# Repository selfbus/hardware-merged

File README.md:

<h1>Selfbus Hardware</h1>
<h2>Main-Branch</h2>
This branch contains <b>all</b> Selfbus hardware items which are needed to build up KNX devices: different types of PCBs, 3D printable tools and enclosures. 

<h2>Other Branches</h2>
Experimental development shall be done within a seperate branch to prevent the main branch getting spammed with dev-commits. 

<h3>Folder structure</h3>
<ul>
<li> addons - item / part / pcb which adds additional functions to a controller, application or module 
<li> applications - applications/devices that require an additional controller board
<li> controller - controller boards
<li> module - devices that do not require a controller board. The controller and the app are merged within one PCB. 
<li> misc - other stuff that is not an EIB bus device
<li> tool - helpers with no functionality without another item
</ul>

<h3>Abbreviations</h3>
<ul>
<li>FM - flush mount (UP Unterputz)
<li>DIN - din rail mountable (für Hutschieneninstallation)
<li>MU - module units (TE Teilungseinheiten); indicates how much space a DIN rail device needs 
<li>*lpc922* - module or controller with lpc922 µC
<li>*lpc1115* - module or controller with lpc1115 µC
<li>TOP / MID / BOT - position where in a DIN rail enclosure a PCB will be mounted
</ul>

<h2>Releases</h2>
The unversioned *.sch and *.brd files indicate development files. 
Once a new version is released, a corresponding folder will be created and copy of the files with the release version appended to the file name will be stored in that folder as well as all other files connected directly to that version (iBom, labels, etc.).

<b>Example: </b>https://github.com/selfbus/hardware-merged/tree/main/modules_lpc1115/smokedetector <br/>
But keep in mind, that this is not implemented in each and every project. In fact it's the exception today (11.05.2023) since a lot of projects are existing within this repository. 
  
<h2>Identify mature hardware</h2>
A warning hint within the readme.md was placed in nearly all projects taken over from hardware-incubation. A folder without that hint contains most likely a stable version taken over from the "hardware" repository. If you are not sure: search for documentation for that device or item at https://selfbus.org or ask the community via https://selfbus.org/forum or https://selfbus.org/chat.

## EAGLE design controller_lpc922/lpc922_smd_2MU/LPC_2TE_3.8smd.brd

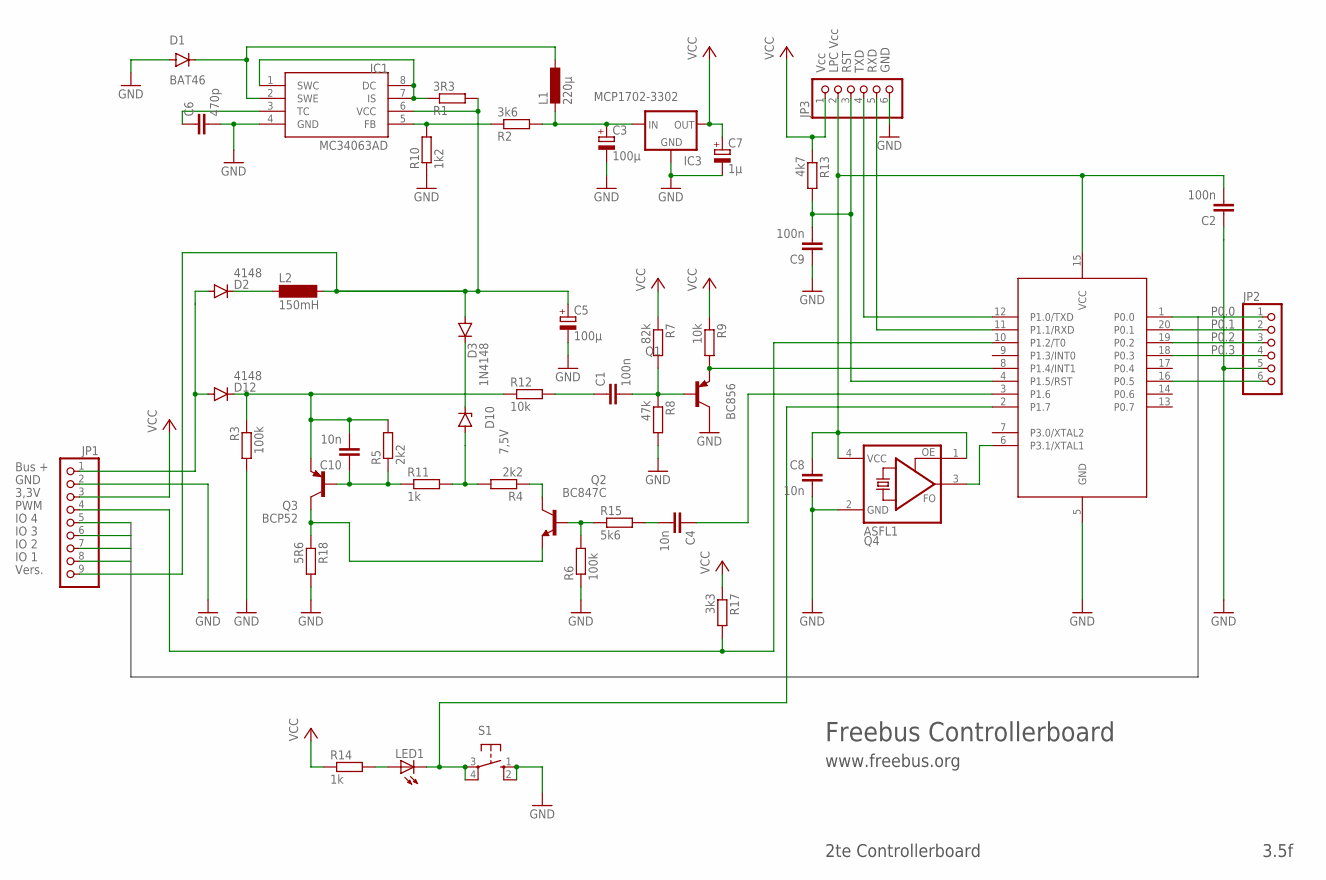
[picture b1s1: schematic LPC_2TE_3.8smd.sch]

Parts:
89LPC922: 89LPC922; DIL20
C1, C2, C9: 100n; C1206
C3: 100µ; E2,5-6
C4, C8, C10: 10n; C1206
C5: 100µ; E3,5-8
C6: 470p; C1206
C7: 1µ; E2-5
D1: BAT46; MINIMELF
D2, D12: 4148; MINIMELF
D3: 1N4148; MINIMELF
D10: 7,5V; DO35Z10
IC1: MC34063AD; SOIC8
IC3: MCP1702-3302; 79LXX
JP1: PINHD-1X9_LONG_2.54; 1X09_LONG
JP2, JP3: PINHD-1X6; 1X06
L1: 220µ; 0207/12
L2: 150mH; BS11
LED1: LED3MM
Q1: BC856; SOT23-BEC
Q2: BC847C; SOT23
Q3: BCP52; SOT223
Q4: ASFL1; ASF
R1: 3R3; R1206
R2: 3k6; R1206
R3, R6: 100k; R1206
R4, R5: 2k2; R1206
R7: 82k; R1206
R8: 47k; R1206
R9, R12: 10k; R1206
R10: 1k2; R1206
R11, R14: 1k; R1206
R13: 4k7; R1206
R15: 5k6; R1206
R17: 3k3; R1206
R18: 5R6; R1206
S1: 10-XX; B3F-10XX

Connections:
/RESET: 89LPC922.4 (P1.5/RST), C9.2, JP3.3, R13.2
BASE: C1.2, Q1.B, R7.2, R8.1
BASE_SEND: Q2.1 (B), R6.2, R15.1
EIB+: D2.A, D12.A, JP1.1
EIB_DC: C5.+, D3.A, IC1.6 (VCC), JP1.9, L2.2, R1.2
FEEDBACK: IC1.5 (FB), R2.1, R10.2
GND: 89LPC922.5 (GND), C2.1, C3.-, C5.-, C6.2, C7.-, C8.2, C9.1, D1.A, IC1.4 (GND), IC3.GND, JP1.2, JP2.5, JP3.6, Q1.C, Q4.2 (GND), R3.2, R6.1, R8.2, R10.1, R18.2, S1.1 (S), S1.2 (S1)
I_SENSE: Q2.2 (E), Q3.2 (C), Q3.4 (C), R18.1
unnamed: Q2.3 (C), R4.1
unnamed: C10.2, D12.C, Q3.3 (E), R3.1, R5.2, R12.1
unnamed: 89LPC922.6 (P3.1/XTAL1), Q4.3 (FO)
unnamed: IC1.1 (SWC), IC1.7 (IS), IC1.8 (DC), R1.1
unnamed: LED1.A, R14.2
unnamed: D2.C, L2.1
unnamed: C6.1, IC1.3 (TC)
unnamed: D3.C, D10.C
unnamed: C1.1, R12.2
unnamed: C4.2, R15.2
unnamed: C10.1, Q3.1 (B), R5.1, R11.1
P0.0: 89LPC922.1 (P0.0), JP1.8, JP2.1
P0.1: 89LPC922.20 (P0.1), JP1.7, JP2.2
P0.2: 89LPC922.19 (P0.2), JP1.6, JP2.3
P0.3: 89LPC922.18 (P0.3), JP1.5, JP2.4
P0.5: 89LPC922.16 (P0.5), JP2.6
PROG: 89LPC922.2 (P1.7), LED1.K (C), S1.3, S1.4 (P1)
PWM: 89LPC922.10 (P1.2/T0), JP1.4, R17.2
REFERENZ: D10.A, R4.2, R11.2
RXD: 89LPC922.11 (P1.1/RXD), JP3.5
SIGIN: 89LPC922.8 (P1.4/INT1), Q1.E, R9.2
SIGOUT: 89LPC922.3 (P1.6), C4.1
SWITCHED: D1.C, IC1.2 (SWE), L1.1
TXD: 89LPC922.12 (P1.0/TXD), JP3.4
VCC: C7.+, IC3.OUT, JP1.3, JP3.1, R7.1, R9.1, R13.1, R14.1, R17.1
VCC_5V: C3.+, IC3.IN, L1.2, R2.2
VCC_LPC: 89LPC922.15 (VCC), C2.2, C8.1, JP3.2, Q4.1 (OE), Q4.4 (VCC)

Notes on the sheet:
Bus +
GND
3,3V
PWM
IO 1
IO 2
IO 3
IO 4
Vcc
LPC Vcc
RST
TXD
RXD
Vers.
Freebus Controllerboard
www.freebus.org
2te Controllerboard
3.5f

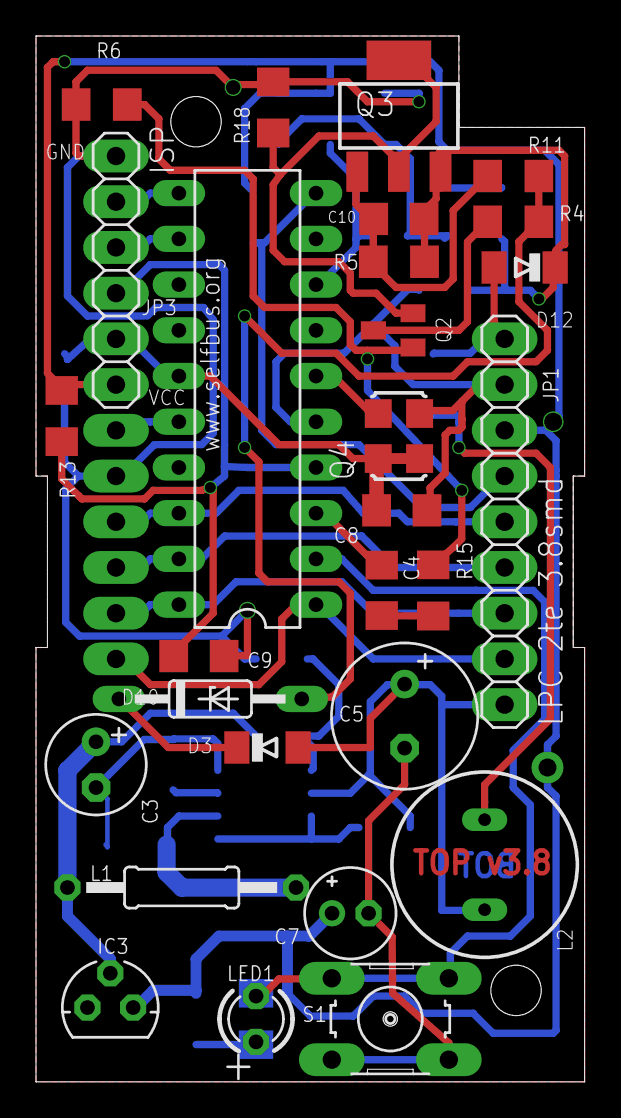
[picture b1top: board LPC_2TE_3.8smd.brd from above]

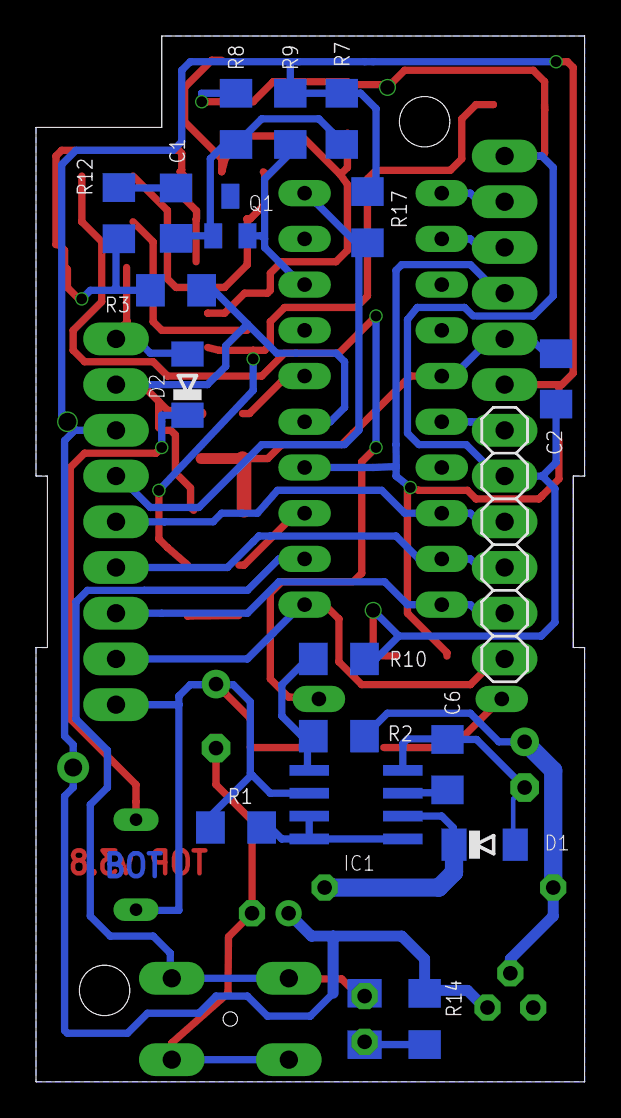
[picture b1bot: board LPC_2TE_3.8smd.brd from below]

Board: 2 copper layers, 30.5 x 58.1 mm, 46 parts (18 on the bottom side), 35 nets.

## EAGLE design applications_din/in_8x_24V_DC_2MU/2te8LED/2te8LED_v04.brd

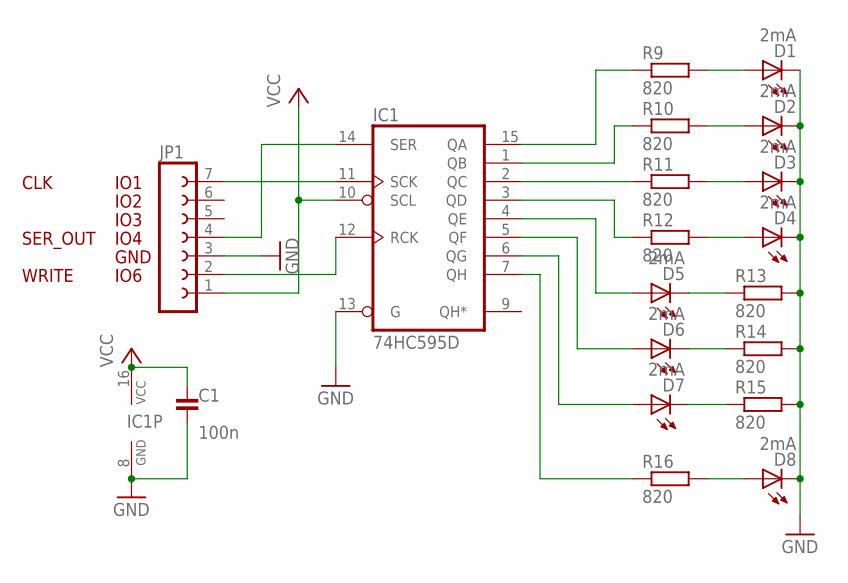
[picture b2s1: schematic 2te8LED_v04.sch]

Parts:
C1: 100n; C0805
D1, D2, D3, D4, D5, D6, D7, D8: 2mA; LED3MM
IC1: 74HC595D; SO16
JP1: FE07-1; FE07
R9, R10, R11, R12, R13, R14, R15, R16: 820; R0805

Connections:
GND: C1.2, D1.K (C), D2.K (C), D3.K (C), D4.K (C), D8.K (C), IC1.8 (GND), IC1.13 (G), JP1.3, R13.2, R14.2, R15.2
IO1: IC1.11 (SCK), JP1.7
IO4: IC1.14 (SER), JP1.4
IO6: IC1.12 (RCK), JP1.2
unnamed: IC1.15 (QA), R9.1
unnamed: IC1.1 (QB), R10.1
unnamed: IC1.2 (QC), R11.1
unnamed: IC1.3 (QD), R12.1
unnamed: D5.A, IC1.4 (QE)
unnamed: D6.A, IC1.5 (QF)
unnamed: D7.A, IC1.6 (QG)
unnamed: D1.A, R9.2
unnamed: D2.A, R10.2
unnamed: D3.A, R11.2
unnamed: D4.A, R12.2
unnamed: D5.K (C), R13.1
unnamed: D6.K (C), R14.1
unnamed: D7.K (C), R15.1
unnamed: IC1.7 (QH), R16.1
unnamed: D8.A, R16.2
VCC: C1.1, IC1.10 (SCL), IC1.16 (VCC), JP1.1

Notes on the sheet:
IO1
IO2
IO3
IO4
IO6
GND
CLK
SER_OUT
WRITE

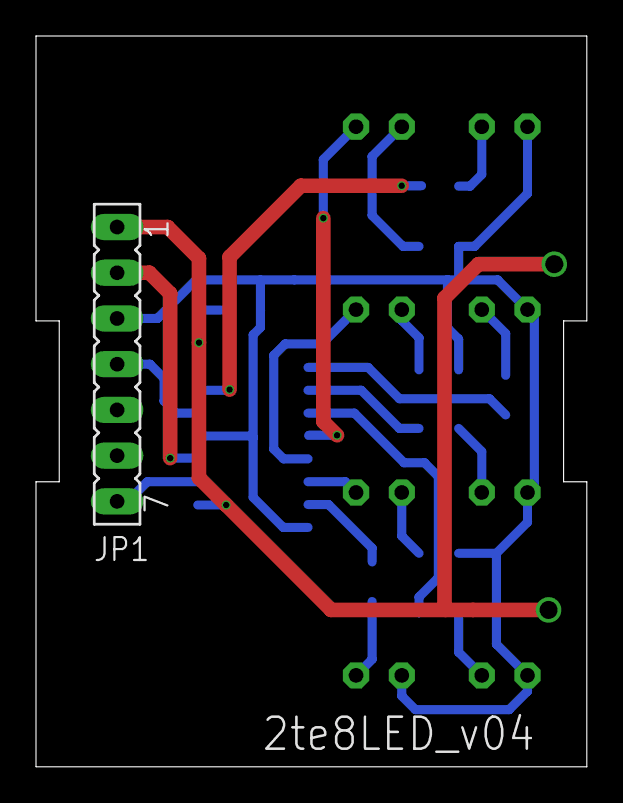
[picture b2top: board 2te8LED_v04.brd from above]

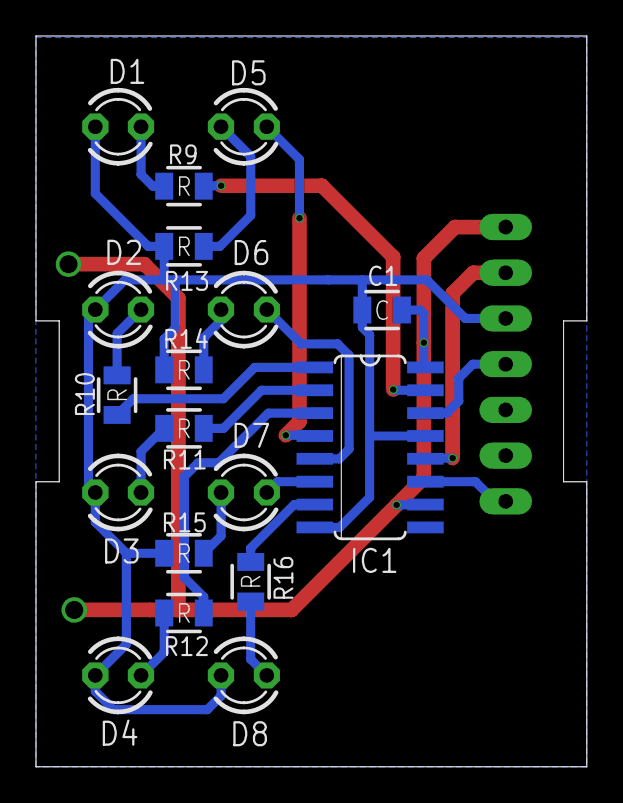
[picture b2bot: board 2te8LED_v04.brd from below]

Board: 2 copper layers, 30.6 x 40.6 mm, 19 parts (18 on the bottom side), 21 nets.

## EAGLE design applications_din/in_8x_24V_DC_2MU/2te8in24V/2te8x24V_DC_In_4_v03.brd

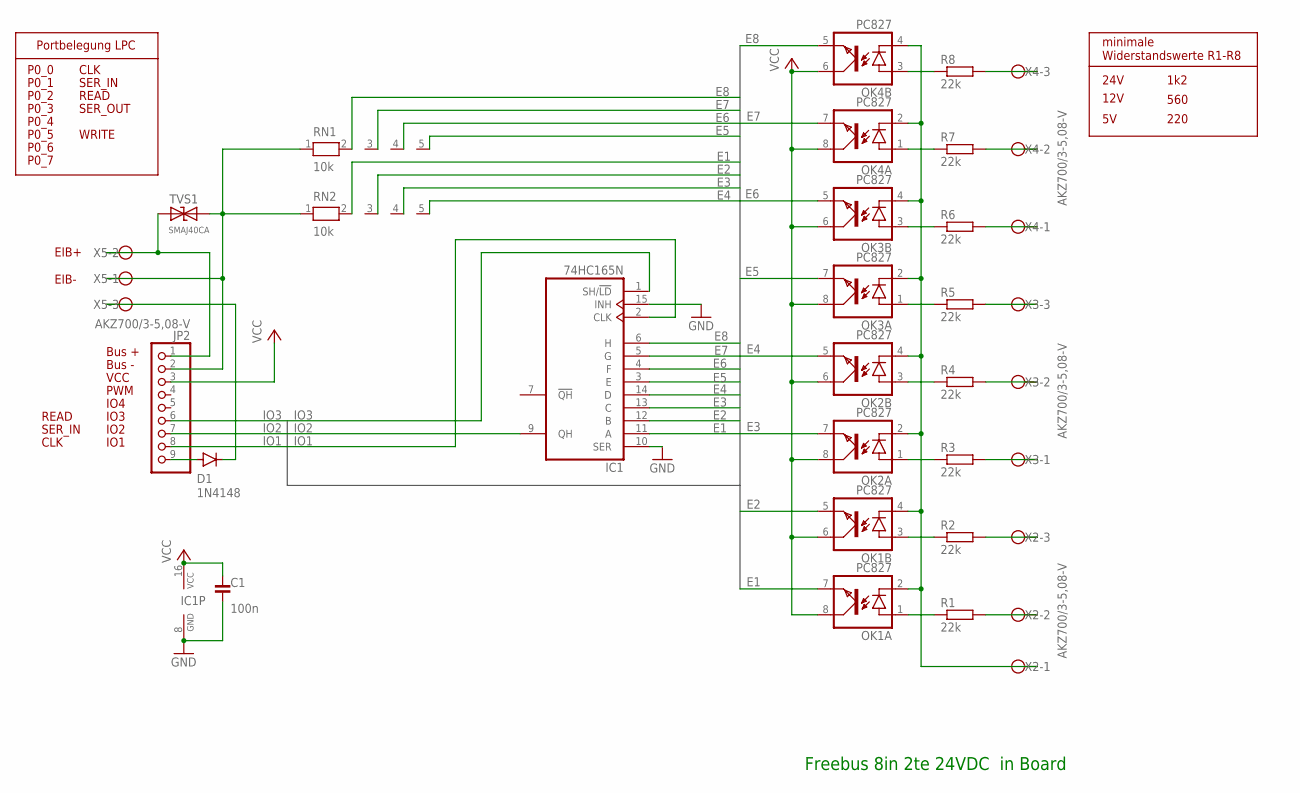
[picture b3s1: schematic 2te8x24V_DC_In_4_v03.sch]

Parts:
C1: 100n; C025-024X044
D1: 1N4148; DO35-7
IC1: 74HC165N; DIL16
JP2: PINHD-1X9; 1X09
OK1, OK2, OK3, OK4: PC827; DIL08
R1, R2, R3, R4, R5, R6, R7, R8: 22k; 0207/10
RN1, RN2: 10k; RN-5
TVS1: SMAJ40CA; DO-214AC(SMA)_BI
X2, X3, X4, X5: AKZ700/3-5,08-V

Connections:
E1: IC1.11 (A), OK1.7 (EMIT), RN2.2
E2: IC1.12 (B), OK1.5 (EMIT), RN2.3
E3: IC1.13 (C), OK2.7 (EMIT), RN2.4
E4: IC1.14 (D), OK2.5 (EMIT), RN2.5
E5: IC1.3 (E), OK3.7 (EMIT), RN1.5
E6: IC1.4 (F), OK3.5 (EMIT), RN1.4
E7: IC1.5 (G), OK4.7 (EMIT), RN1.3
E8: IC1.6 (H), OK4.5 (EMIT), RN1.2
EIB+: JP2.1, TVS1.2 (A2), X5.2
GND: C1.2, IC1.8 (GND), IC1.10 (SER), IC1.15 (INH), JP2.2, RN1.1, RN2.1, TVS1.1 (A1), X5.1
GND24: OK1.2 (C), OK1.4 (C), OK2.2 (C), OK2.4 (C), OK3.2 (C), OK3.4 (C), OK4.2 (C), OK4.4 (C), X2.1
IO1: IC1.2 (CLK), JP2.8
IO2: IC1.9 (QH), JP2.7
IO3: IC1.1 (SH/!LD), JP2.6
unnamed: D1.C, X5.3
unnamed: OK1.1 (A), R1.1
unnamed: R1.2, X2.2
unnamed: OK1.3 (A), R2.1
unnamed: R2.2, X2.3
unnamed: OK2.1 (A), R3.1
unnamed: R3.2, X3.1
unnamed: OK2.3 (A), R4.1
unnamed: R4.2, X3.2
unnamed: OK3.1 (A), R5.1
unnamed: R5.2, X3.3
unnamed: OK3.3 (A), R6.1
unnamed: R6.2, X4.1
unnamed: OK4.1 (A), R7.1
unnamed: R7.2, X4.2
unnamed: OK4.3 (A), R8.1
unnamed: R8.2, X4.3
unnamed: D1.A, JP2.9
VCC: C1.1, IC1.16 (VCC), JP2.3, OK1.6 (COL), OK1.8 (COL), OK2.6 (COL), OK2.8 (COL), OK3.6 (COL), OK3.8 (COL), OK4.6 (COL), OK4.8 (COL)

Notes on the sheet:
Freebus 8in 2te 24VDC in Board
Bus +
Bus -
VCC
PWM
IO1
IO2
IO3
IO4
SER_IN
CLK
READ
EIB+
EIB-
SER_OUT
WRITE
P0_0
P0_1
P0_2
P0_3
P0_4
P0_5
P0_6
P0_7
Portbelegung LPC
24V
12V
1k2
560
220
minimale Widerstandswerte R1-R8

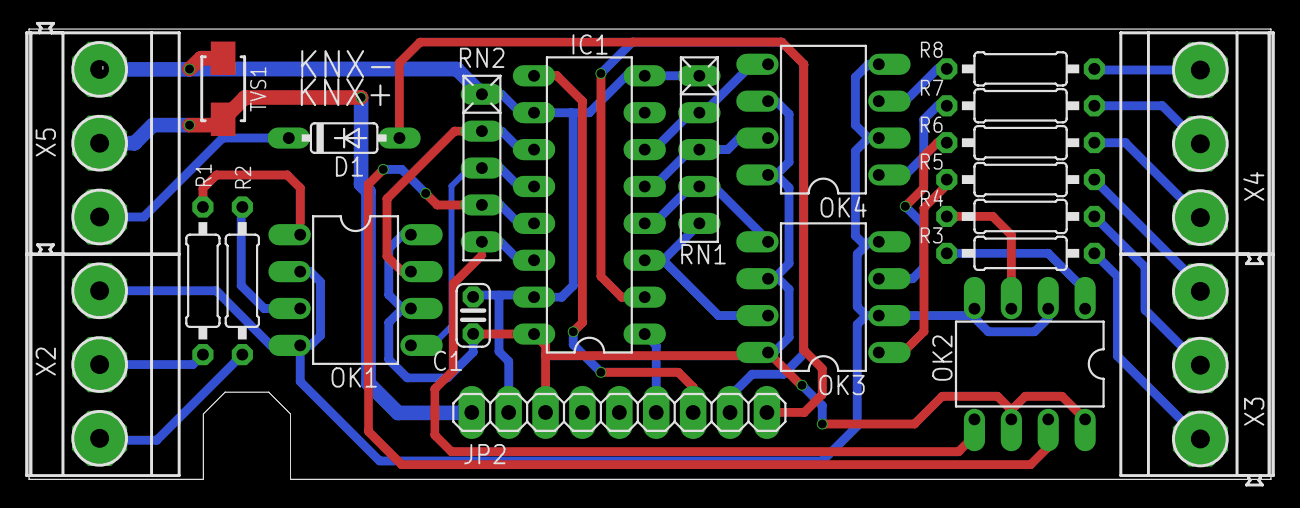
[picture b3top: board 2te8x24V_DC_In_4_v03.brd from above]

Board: 2 copper layers, 85.5 x 31.0 mm, 23 parts (0 on the bottom side), 33 nets.

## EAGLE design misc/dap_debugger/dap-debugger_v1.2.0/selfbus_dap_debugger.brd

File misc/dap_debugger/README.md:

# SBDAP - Selfbus DAP Adapter
Project documentation: https://selfbus.org/wiki/devices/tools-sonstiges/69-sbdap-selfbus-debug-adapter

Forum discussions: [https://selfbus.org/forum/app.php/tag/SBDAP](https://selfbus.org/forum/app.php/tag/SBDAP)

|Version|Description                          |
|-------|-------------------------------------|
|v1.0.0 |first release version                |
|v1.1.0 |USB-C connection instead of Micro-USB|
|v1.2.0 |IC2 package switched to SOT363/SC70  |

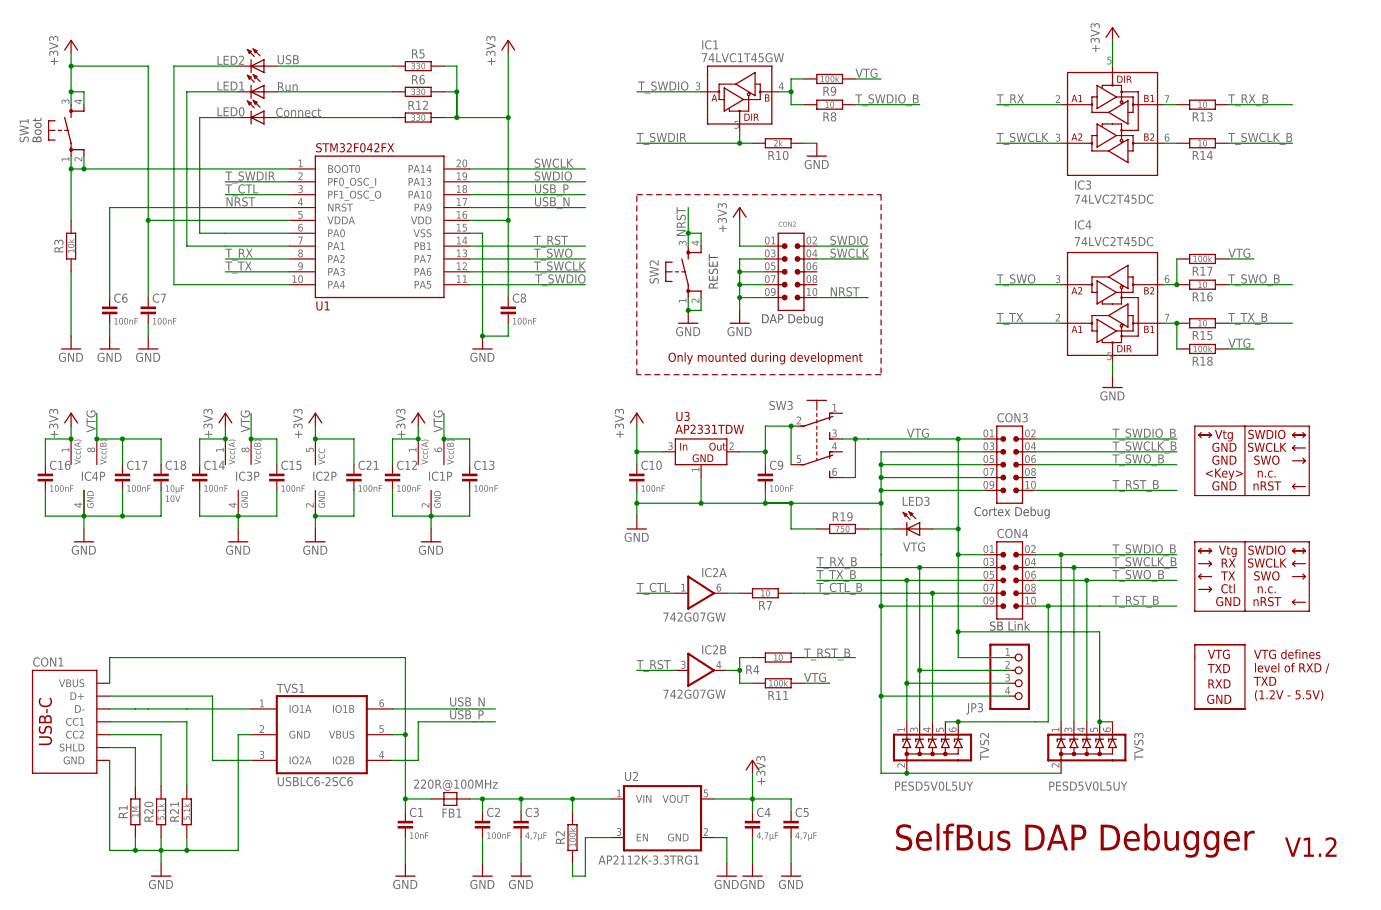
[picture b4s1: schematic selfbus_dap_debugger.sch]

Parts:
C1: 10nF; C0805
C2, C6, C7, C8, C9, C10, C12, C13, C14, C15, C16, C17, C21: 100nF; C0805
C3, C4, C5: 4,7µF; C0805
C18: 10µF; C0805; VOLTAGE 10V
CON1: XKB U262-161N-4BVC11; USB-C-16P-2LAYER-PADS
CON2, CON3: SHF-105-01-X-D-TH; SAMTEC_SHF-105-01-X-D-TH
CON4: SAMTEC-LTMM-105-02-T-D
FB1: 220R@100MHz; FB0805; MOUSER# 810-MPZ2012S221ATD25; LCSC#2 C139188
IC1: 74LVC1T45GW; SOT363; MOUSER# 771-74LVC1T45GW125; LCSC# C478004
IC2: 742G07GW; SOT363; PART# 74LVC2G07GW,125; LCSC# C24478
IC3: 74LVC2T45DC; VSSOP8(0.5); MOUSER# 595-SN74LVC2T45DCUT; LCSC# C15741
IC4: 74LVC2T45DC; VSSOP8(0.5)
JP3: PINHD-1X4; 1X04
LED0: Connect; LED_3MM_GREEN
LED1: Run; LED_3MM_YELLOW
LED2: USB; LED_3MM_GREEN
LED3: VTG; LED_3MM_RED
R1: 1M; R0805
R2, R9, R11, R17, R18: 100k; R0805
R3: 10k; R0805
R4, R7, R8, R13, R14, R15, R16: 10; R0805
R5, R6, R12: 330; R0805
R10: 2k; R0805
R19: 750; R0805
R20, R21: 5,1k; R0805
SW1: BOOT; TACT_SWITCH_6X6_SNAP-IN_17; MOUSER# 688-SKHHDHA010; LCSC# C139811
SW2: RESET; TACT_SWITCH_6X6_SNAP-IN_17; MOUSER# 688-SKHHDHA010; LCSC# C139811
SW3: XKB7070-Z; XKB7070
TVS1: USBLC6-2SC6; SOT-23-6L; MOUSER# 511-USBLC6-2SC6; LCSC#2 C2687116
TVS2: PESD5V0L5UY; SOT363; MOUSER# 771-PESD5V0L5UY-T/R; LCSC# C179747
TVS3: PESD5V0L5UY; SOT363
U1: STM32F042FX; TSSOP20; MOUSER# 511-STM32F042F4P6; LCSC# C81002
U2: AP2112K-3.3TRG1; SOT23-5; MOUSER# 621-AP2112K-3.3TRG1; LCSC# C51118
U3: AP2331TDW; SC59; MOUSER# 621-AP2331W-7; LCSC# C460346

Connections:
+3V3: C4.1, C5.1, C7.1, C8.1, C10.1, C12.1, C14.1, C16.1, C21.1, CON2.01 (1), IC1.1 (VCC(A)), IC2.5 (VCC), IC3.1 (VCC(A)), IC3.5 (DIR), IC4.1 (VCC(A)), R5.2, R6.2, R12.2, SW1.3, SW1.4, U1.5 (VDDA), U1.16 (VDD), U2.5 (VOUT), U3.3 (IN)
D_N: CON1.A7 (D-), CON1.B7 (D-), TVS1.1 (IO1A)
D_P: CON1.A6 (D+), CON1.B6 (D+), TVS1.3 (IO2A)
GND: C1.2, C2.2, C3.2, C4.2, C5.2, C6.2, C7.2, C8.2, C9.2, C10.2, C12.2, C13.2, C14.2, C15.2, C16.2, C17.2, C18.2, C21.2, CON1.GND, CON1.GND2 (GND), CON2.03 (3), CON2.05 (5), CON2.07 (7), CON2.09 (9), CON3.03 (3), CON3.05 (5), CON3.07 (7), CON3.09 (9), CON4.09 (9), IC1.2 (GND), IC2.2 (GND), IC3.4 (GND), IC4.4 (GND), IC4.5 (DIR), JP3.4, R1.1, R3.1, R10.1, R19.1, R20.1, R21.1, SW2.1, SW2.2, TVS1.2 (GND), TVS2.2 (A), TVS3.2 (A), U1.15 (VSS), U2.2 (GND), U3.1 (GND)
LED0: LED0.C, U1.6 (PA0)
LED1: LED1.C, U1.7 (PA1)
unnamed: CON1.SHLD1 (SHLD), CON1.SHLD2 (SHLD), CON1.SHLD3 (SHLD), CON1.SHLD4 (SHLD), R1.2
unnamed: CON1.B5 (CC2), R20.2
unnamed: CON1.A5 (CC1), R21.2
unnamed: R2.1, U2.3 (EN)
unnamed: C2.1, C3.1, FB1.2, R2.2, U2.1 (VIN)
unnamed: IC2.4 (OUT), R4.2, R11.2
unnamed: IC2.6 (OUT), R7.2
unnamed: R3.2, SW1.1, SW1.2, U1.1 (BOOT0)
unnamed: LED2.A, R5.1
unnamed: LED1.A, R6.1
unnamed: C9.1, SW3.2, SW3.5, U3.2 (OUT)
unnamed: LED0.A, R12.1
unnamed: IC3.7 (B1), R13.2
unnamed: IC3.6 (B2), R14.2
unnamed: IC4.6 (B2), R16.2, R17.2
unnamed: IC4.7 (B1), R15.2, R18.2
unnamed: IC1.4 (B), R8.2, R9.2
unnamed: LED2.C, U1.10 (PA4)
unnamed: LED3.C, R19.2
NRST: C6.1, CON2.10, SW2.3, SW2.4, U1.4 (NRST)
SWCLK: CON2.04 (4), U1.20 (PA14)
SWDIO: CON2.02 (2), U1.19 (PA13)
T_CTL: IC2.1 (IN), U1.3 (PF1_OSC_O)
T_CTL_B: CON4.07 (7), R7.1, TVS2.4 (C3)
T_RST: IC2.3 (IN), U1.14 (PB1)
T_RST_B: CON3.10, CON4.10, R4.1, TVS2.5 (C4), TVS2.6 (C5)
T_RX: IC3.2 (A1), U1.8 (PA2)
T_RX_B: CON4.03 (3), JP3.2, R13.1, TVS2.3 (C2)
T_SWCLK: IC3.3 (A2), U1.12 (PA6)
T_SWCLK_B: CON3.04 (4), CON4.04 (4), R14.1, TVS3.3 (C2)
T_SWDIO: IC1.3 (A), U1.11 (PA5)
T_SWDIO_B: CON3.02 (2), CON4.02 (2), R8.1, TVS3.1 (C1)
T_SWDIR: IC1.5 (DIR), R10.2, U1.2 (PF0_OSC_I)
T_SWO: IC4.3 (A2), U1.13 (PA7)
T_SWO_B: CON3.06 (6), CON4.06 (6), R16.1, TVS3.4 (C3)
T_TX: IC4.2 (A1), U1.9 (PA3)
T_TX_B: CON4.05 (5), JP3.3, R15.1, TVS2.1 (C1)
USB_N: TVS1.6 (IO1B), U1.17 (PA9)
USB_P: TVS1.4 (IO2B), U1.18 (PA10)
VBUS: C1.1, CON1.VBUS1 (VBUS), CON1.VBUS2 (VBUS), FB1.1, TVS1.5 (VBUS)
VTG: C13.1, C15.1, C17.1, C18.1, CON3.01 (1), CON4.01 (1), IC1.6 (VCC(B)), IC3.8 (VCC(B)), IC4.8 (VCC(B)), JP3.1, LED3.A, R9.1, R11.1, R17.1, R18.1, SW3.3 (S), SW3.6 (S), TVS3.5 (C4), TVS3.6 (C5)

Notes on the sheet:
SelfBus DAP Debugger
V1.2
DAP Debug
Only mounted during development
SB Link
Cortex Debug
Vtg
GND
Ctl
SWDIO
SWCLK
SWO
nRST
<Key>
n.c.
TXD
RXD
VTG
VTG defines level of RXD / TXD (1.2V - 5.5V)
Boot
RESET

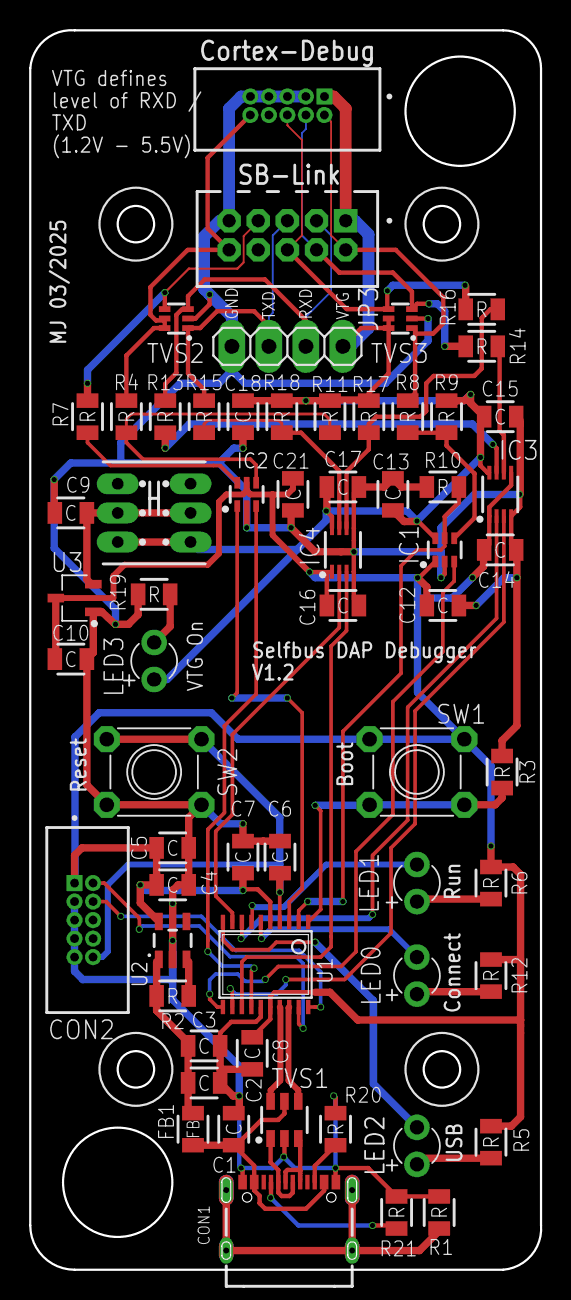
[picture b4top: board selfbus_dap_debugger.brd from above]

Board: 2 copper layers, 35.1 x 85.1 mm, 62 parts (0 on the bottom side), 47 nets.

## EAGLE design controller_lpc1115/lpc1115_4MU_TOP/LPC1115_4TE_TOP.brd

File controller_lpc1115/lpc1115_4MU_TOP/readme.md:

Ein Controller für 4TE breite Gehäuse. Zur Steuerung von Applikationsplatinen.</br>
Dieser Controller wird in die oberste Lage (TOP) eingebaut und hat die Option LEDs / Taster zu bestücken bereits an Bord. 

Er findet Verwendung z.B. im 6-fach strommessenden Schaltaktor oder im 8out mit Energy-Storage. 
https://selfbus.org/wiki/devices/outputs/22-switching-actuator-6x-current-sensing-230v-16a-6mount-units

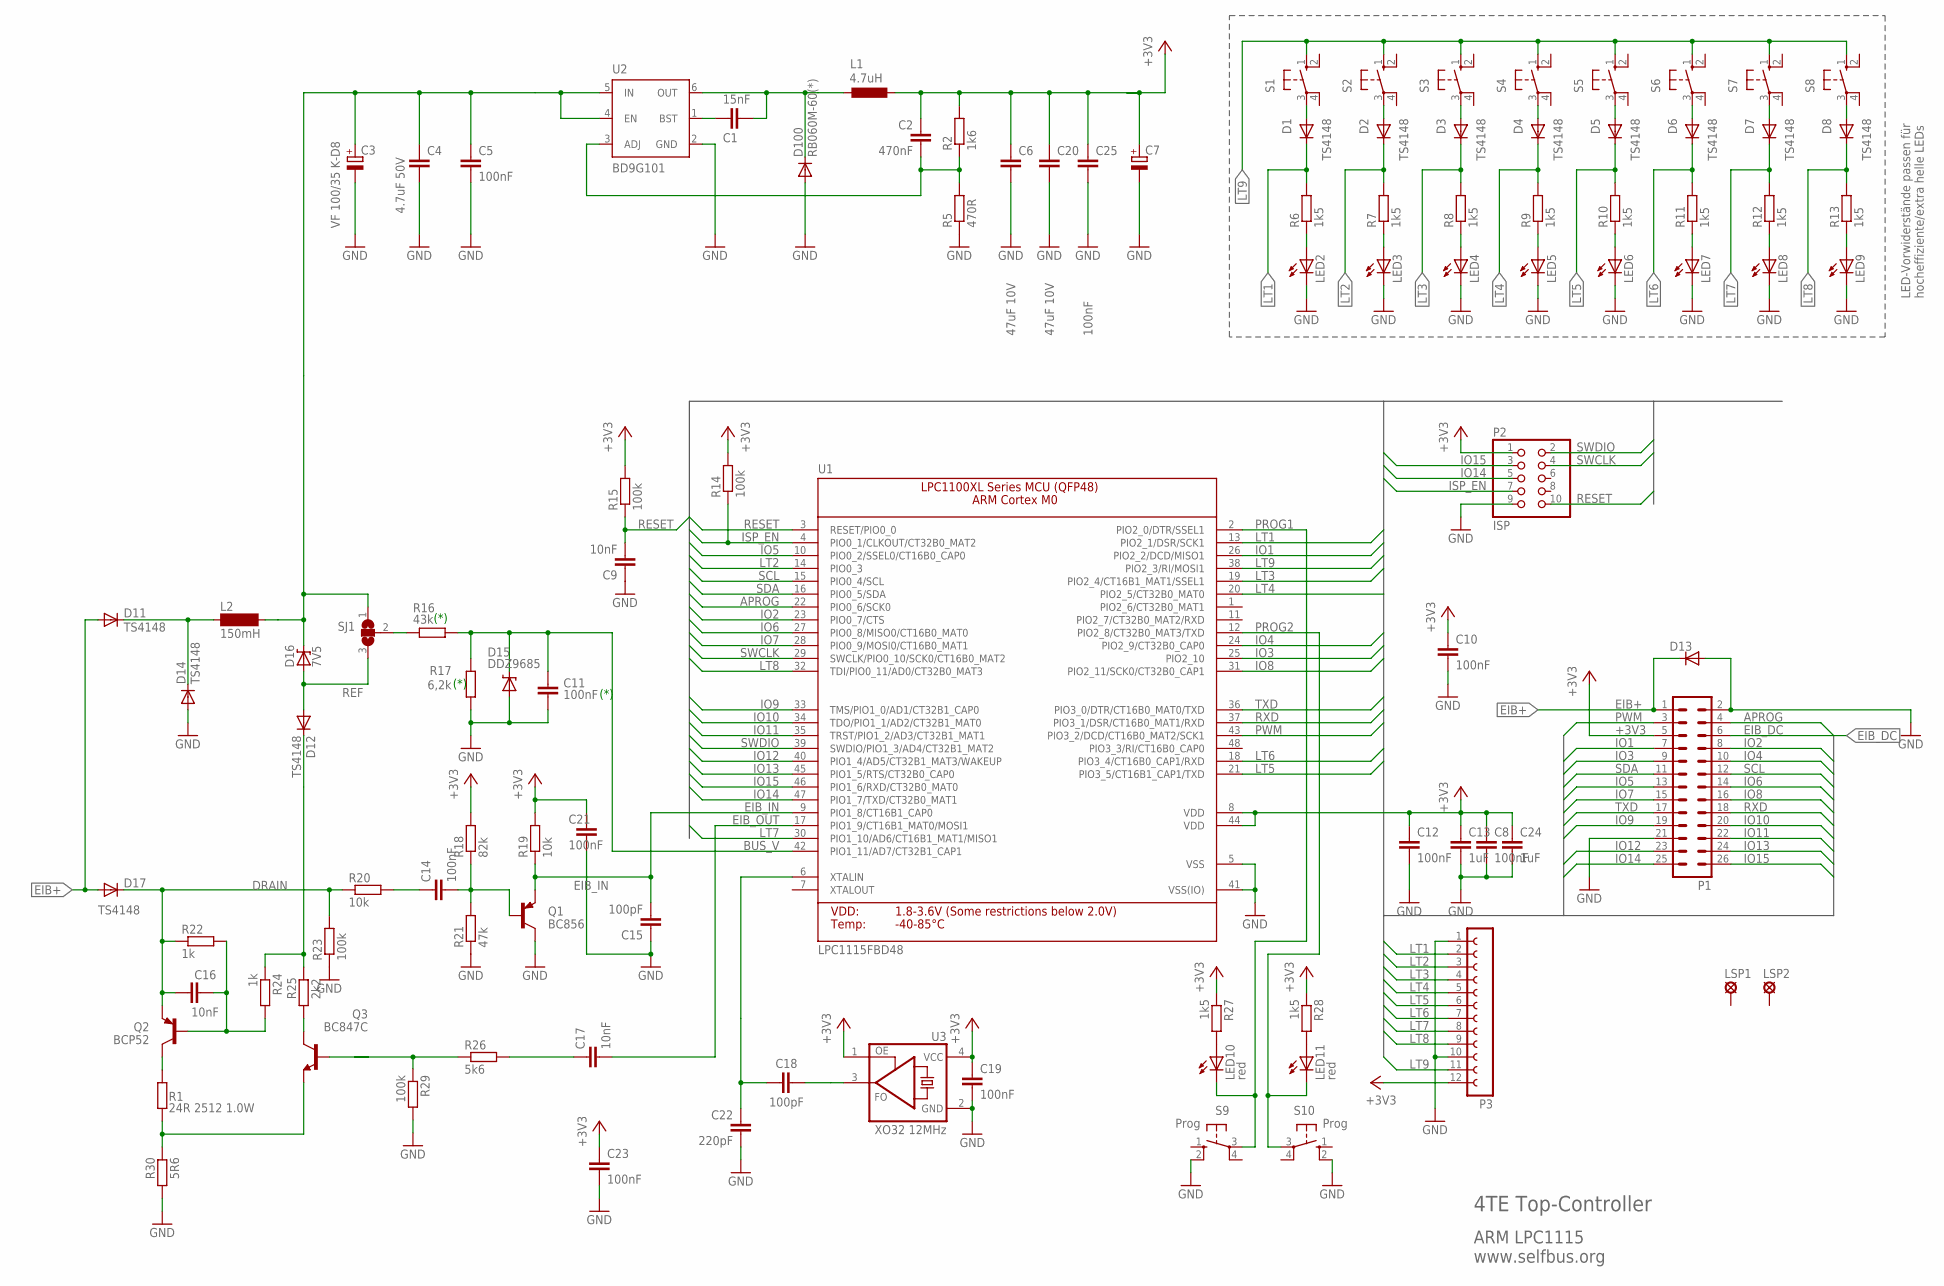
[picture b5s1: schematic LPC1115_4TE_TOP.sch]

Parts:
C1: 15nF; C0805
C2: 470nF; C0805
C3: VF 100/35 K-D8; ESMD-D
C4: 4.7uF 50V; C0805
C5, C8, C10, C11, C12, C14, C19, C21, C23: 100nF; C0805
C6, C20: 47uF 10V; C0805
C7: 100uF; ESMD-D
C9, C16, C17: 10nF; C0805
C13, C24: 1uF; C0805
C15, C18: 100pF; C0805
C22: 220pF; C0805
C25: 100nF; C1206
D1, D2, D3, D4, D5, D6, D7, D8, D11, D12, D14, D17: TS4148; D0805
D13: SMAJ40AC; SMB
D15: DDZ9685; SOD-123
D16: 7V5; SOD-123
D100: RB060M-60(*); SOD123
L1: 4.7uH; L4532P
L2: 150mH; BS11_LIEGEND
LED2, LED3, LED4, LED5, LED6, LED7, LED8, LED9: LEDSMT1206; 1206
LED10, LED11: red; 1206
LSP1, LSP2: SE13_SM
P1: ML26
P2: ISP; 2X05M
P3: FE12-1; FE12
Q1: BC856; SOT23-BEC
Q2: BCP52; SOT223
Q3: BC847C; SOT23
R1: 24R 2512 1.0W; R2512
R2: 1k6; R0805
R5: 470R; R0805
R6, R7, R8, R9, R10, R11, R12, R13, R27, R28: 1k5; R0805
R14, R15, R23, R29: 100k; R0805
R16: 43k; R0805
R17: 6,2k; R0805
R18: 82k; R0805
R19, R20: 10k; R0805
R21: 47k; R0805
R22, R24: 1k; R0805
R25: 2k2; R0805
R26: 5k6; R0805
R30: 5R6; R0805
S1, S2, S3, S4, S5, S6, S7, S8: 10-XXSMD; B3F-10XX_SMD
S9, S10: Prog; B3F-10XX_SMD
SJ1: SJ2W; SJ_2
U1: LPC1115FBD48; LQFP48
U2: BD9G101; SOT23-6MOD
U3: XO32 12MHz; ASF

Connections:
+3V3: C2.1, C6.1, C7.+, C8.1, C10.1, C12.1, C13.1, C19.1, C20.1, C21.2, C23.1, C24.1, C25.1, L1.2, P1.5, P2.1, P3.12, R2.2, R14.2, R15.2, R18.2, R19.2, R27.1, R28.1, U1.8 (VDD), U1.44 (VDD), U3.1 (OE), U3.4 (VCC)
APROG: P1.4, U1.22 (PIO0_6/SCK0)
BUS_V: C11.1, D15.C, R16.2, R17.1, U1.42 (PIO1_11/AD7/CT32B1_CAP1)
DRAIN: C16.1, D17.C, Q2.3 (E), R20.1, R22.1, R23.2
EIB+: D11.A, D13.1 (C), D17.A, P1.1
EIB_DC: C3.+, C4.1, C5.1, D16.C, L2.2, P1.6, SJ1.1, U2.4 (EN), U2.5 (IN)
EIB_IN: C15.2, Q1.E, R19.1, U1.9 (PIO1_8/CT16B1_CAP0)
EIB_OUT: C17.2, U1.17 (PIO1_9/CT16B1_MAT0/MOSI1)
GND: C3.-, C4.2, C5.2, C6.2, C7.-, C8.2, C9.1, C10.2, C11.2, C12.2, C13.2, C15.1, C19.2, C20.2, C21.1, C22.2, C23.2, C24.2, C25.2, D13.2 (A), D14.A, D15.A, D100.A, LED2.C, LED3.C, LED4.C, LED5.C, LED6.C, LED7.C, LED8.C, LED9.C, P1.2, P1.21, P2.9, P3.1, P3.10, Q1.C, R5.1, R17.2, R21.1, R23.1, R29.2, R30.1, S9.2 (S1), S10.2 (S1), U1.5 (VSS), U1.41 (VSS(IO)), U2.2 (GND), U3.2 (GND)
IO1: P1.7, U1.26 (PIO2_2/DCD/MISO1)
IO2: P1.8, U1.23 (PIO0_7/CTS)
IO3: P1.9, U1.25 (PIO2_10)
IO4: P1.10, U1.24 (PIO2_9/CT32B0_CAP0)
IO5: P1.13, U1.10 (PIO0_2/SSEL0/CT16B0_CAP0)
IO6: P1.14, U1.27 (PIO0_8/MISO0/CT16B0_MAT0)
IO7: P1.15, U1.28 (PIO0_9/MOSI0/CT16B0_MAT1)
IO8: P1.16, U1.31 (PIO2_11/SCK0/CT32B0_CAP1)
IO9: P1.19, U1.33 (TMS/PIO1_0/AD1/CT32B1_CAP0)
IO10: P1.20, U1.34 (TDO/PIO1_1/AD2/CT32B1_MAT0)
IO11: P1.22, U1.35 (TRST/PIO1_2/AD3/CT32B1_MAT1)
IO12: P1.23, U1.40 (PIO1_4/AD5/CT32B1_MAT3/WAKEUP)
IO13: P1.24, U1.45 (PIO1_5/RTS/CT32B0_CAP0)
IO14: P1.25, P2.5, U1.47 (PIO1_7/TXD/CT32B0_MAT1)
IO15: P1.26, P2.3, U1.46 (PIO1_6/RXD/CT32B0_MAT0)
ISP_EN: P2.7, R14.1, U1.4 (PIO0_1/CLKOUT/CT32B0_MAT2)
LT1: D1.C, P3.2, R6.2, U1.13 (PIO2_1/DSR/SCK1)
LT2: D2.C, P3.3, R7.2, U1.14 (PIO0_3)
LT3: D3.C, P3.4, R8.2, U1.19 (PIO2_4/CT16B1_MAT1/SSEL1)
LT4: D4.C, P3.5, R9.2, U1.20 (PIO2_5/CT32B0_MAT0)
LT5: D5.C, P3.6, R10.2, U1.21 (PIO3_5/CT16B1_CAP1/TXD)
LT6: D6.C, P3.7, R11.2, U1.18 (PIO3_4/CT16B0_CAP1/RXD)
LT7: D7.C, P3.8, R12.2, U1.30 (PIO1_10/AD6/CT16B1_MAT1/MISO1)
LT8: D8.C, P3.9, R13.2, U1.32 (TDI/PIO0_11/AD0/CT32B0_MAT3)
LT9: P3.11, S1.1 (S), S2.1 (S), S3.1 (S), S4.1 (S), S5.1 (S), S6.1 (S), S7.1 (S), S8.1 (S), U1.38 (PIO2_3/RI/MOSI1)
LX: C1.1, D100.C, L1.1, U2.6 (OUT)
unnamed: C17.1, R26.2
unnamed: C14.1, R20.2
unnamed: LED11.A, R28.2
unnamed: R16.1, SJ1.2
unnamed: Q3.3 (C), R25.1
unnamed: Q3.2 (E), R1.1, R30.2
unnamed: D11.C, D14.C, L2.1
unnamed: Q2.2 (C), Q2.4 (C), R1.2
unnamed: Q3.1 (B), R26.1, R29.1
unnamed: C14.2, Q1.B, R18.1, R21.2
unnamed: C16.2, Q2.1 (B), R22.2, R24.2
unnamed: C18.1, U3.3 (FO)
unnamed: D8.A, S8.3
unnamed: C1.2, U2.1 (BST)
unnamed: D7.A, S7.3
unnamed: C2.2, R2.1, R5.2, U2.3 (ADJ)
unnamed: LED2.A, R6.1
unnamed: D6.A, S6.3
unnamed: D5.A, S5.3
unnamed: D4.A, S4.3
unnamed: D3.A, S3.3
unnamed: D2.A, S2.3
unnamed: LED3.A, R7.1
unnamed: D1.A, S1.3
unnamed: LED10.A, R27.2
unnamed: LED4.A, R8.1
unnamed: LED5.A, R9.1
unnamed: LED6.A, R10.1
unnamed: LED7.A, R11.1
unnamed: LED8.A, R12.1
unnamed: LED9.A, R13.1
unnamed: D12.C, R24.1, R25.2
PROG1: LED10.C, S9.3, U1.2 (PIO2_0/DTR/SSEL1)
PROG2: LED11.C, S10.3, U1.12 (PIO2_8/CT32B0_MAT3/TXD)
PWM: P1.3, U1.43 (PIO3_2/DCD/CT16B0_MAT2/SCK1)
REF: D12.A, D16.A, SJ1.3
RESET: C9.2, P2.10, R15.1, U1.3 (RESET/PIO0_0)
RXD: P1.18, U1.37 (PIO3_1/DSR/CT16B0_MAT1/RXD)
SCL: P1.12, U1.15 (PIO0_4/SCL)
SDA: P1.11, U1.16 (PIO0_5/SDA)
SWCLK: P2.4, U1.29 (SWCLK/PIO0_10/SCK0/CT16B0_MAT2)
SWDIO: P2.2, U1.39 (SWDIO/PIO1_3/AD4/CT32B1_MAT2)
TXD: P1.17, U1.36 (PIO3_0/DTR/CT16B0_MAT0/TXD)
XTALIN: C18.2, C22.1, U1.6 (XTALIN)

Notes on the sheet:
4TE Top-Controller
ARM LPC1115 www.selfbus.org
LED-Vorwiderstände passen für hocheffiziente/extra helle LEDs
(*)

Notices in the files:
parts and their libraries:
microbuilder: This work is placed in the public domain, and may be freely used for commercial and non-commercial work with the following conditions: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
